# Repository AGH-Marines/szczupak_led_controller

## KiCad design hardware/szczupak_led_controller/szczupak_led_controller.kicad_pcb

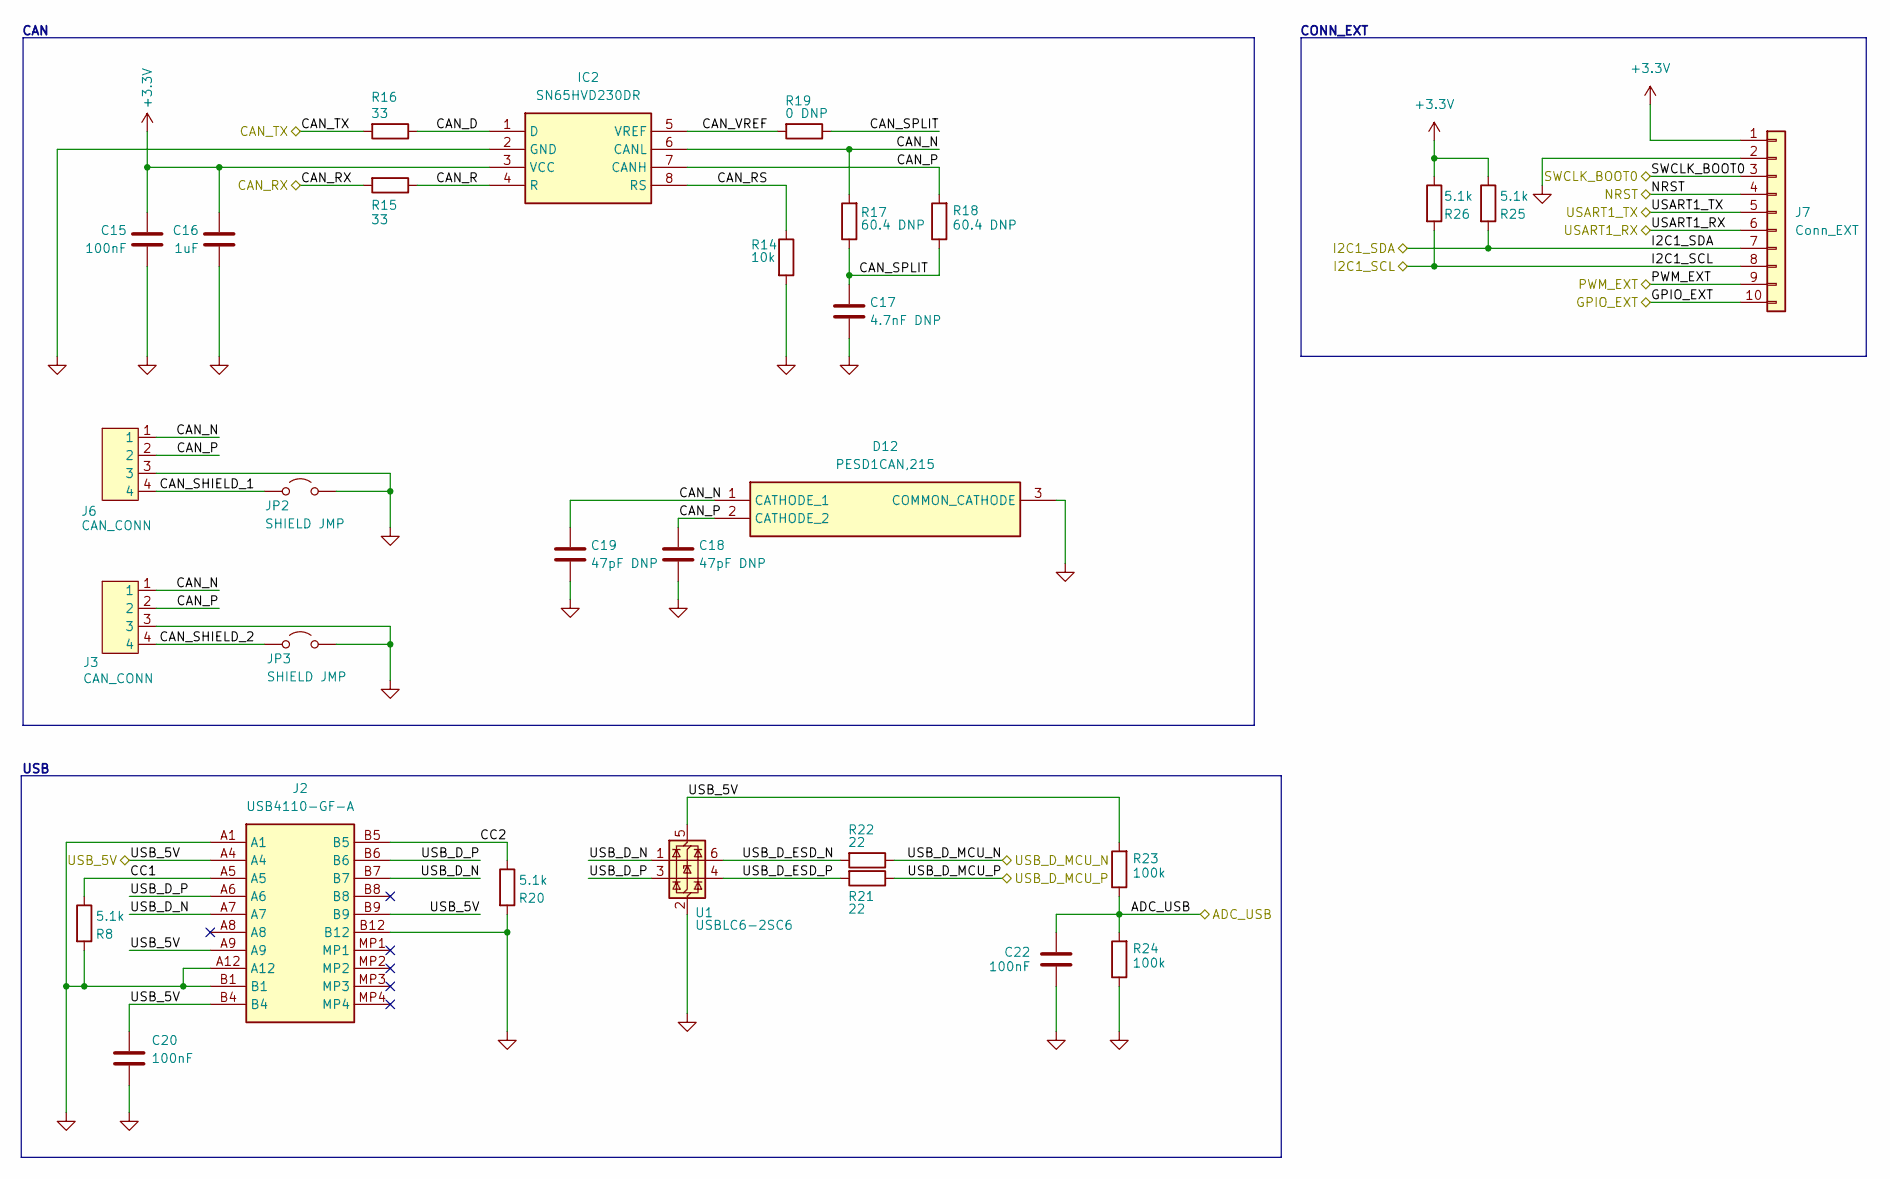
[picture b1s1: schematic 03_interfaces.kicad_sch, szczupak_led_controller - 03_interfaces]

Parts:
C15, C20, C22: 100nF; C_0603_1608Metric
C16: 1uF; C_0805_2012Metric
C17: 4.7nF DNP; C_0603_1608Metric
C18, C19: 47pF DNP; C_0603_1608Metric
D12: PESD1CAN,215; SOT95P230X110-3N; Manufacturer_Part_Number PESD1CAN,215
IC2: SN65HVD230DR; SOT127P600X175-8N; Manufacturer_Part_Number SN65HVD230DR; Mouser Part Number 595-SN65HVD230DR
J2: USB4110-GF-A; USB4110GFA; Manufacturer_Part_Number USB4110-GF-A
J3, J6: CAN_CONN; XY2500V-D(5.08)-4PIN
J7: Conn_EXT; PinHeader_1x10_P2.54mm_Vertical
JP2, JP3: SHIELD JMP; SolderJumper-2_P1.3mm_Open_TrianglePad1.0x1.5mm
R8, R20, R25, R26: 5.1k; R_0603_1608Metric
R14: 10k; R_0603_1608Metric
R15, R16: 33; R_0603_1608Metric
R17, R18: 60.4 DNP; R_0805_2012Metric
R19: 0 DNP; R_0603_1608Metric
R21, R22: 22; R_0603_1608Metric
R23, R24: 100k; R_0603_1608Metric
U1: USBLC6-2SC6; SOT-23-6

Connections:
+3.3V: C15.1, C16.1, IC2.3 (VCC), J7.1, R25.1, R26.1; also elsewhere on the board
/03_interfaces/CAN_D: IC2.1 (D), R16.1
/03_interfaces/CAN_N: C19.1, D12.1 (CATHODE_1), IC2.6 (CANL), J3.1, J6.1, R17.2
/03_interfaces/CAN_P: C18.1, D12.2 (CATHODE_2), IC2.7 (CANH), J3.2, J6.2, R18.2
/03_interfaces/CAN_R: IC2.4 (R), R15.1
/03_interfaces/CAN_RS: IC2.8 (RS), R14.1
/03_interfaces/CAN_SHIELD_1: J6.4, JP2.1 (A)
/03_interfaces/CAN_SHIELD_2: J3.4, JP3.1 (A)
/03_interfaces/CAN_SPLIT: C17.1, R17.1, R18.1, R19.1
/03_interfaces/CAN_VREF: IC2.5 (VREF), R19.2
/03_interfaces/CC1: J2.A5, R8.1
/03_interfaces/CC2: J2.B5, R20.1
/03_interfaces/USB_D_ESD_N: R22.2, U1.6 (I/O1)
/03_interfaces/USB_D_ESD_P: R21.2, U1.4 (I/O2)
/03_interfaces/USB_D_N: J2.A7, J2.B7, U1.1 (I/O1)
/03_interfaces/USB_D_P: J2.A6, J2.B6, U1.3 (I/O2)
/ADC_USB: C22.1, R23.1, R24.2; also elsewhere on the board
/CAN_RX: R15.2; also elsewhere on the board
/CAN_TX: R16.2; also elsewhere on the board
/GPIO_EXT: J7.10; also elsewhere on the board
/I2C1_SCL: J7.8, R26.2; also elsewhere on the board
/I2C1_SDA: J7.7, R25.2; also elsewhere on the board
/NRST: J7.4; also elsewhere on the board
/PWM_EXT: J7.9; also elsewhere on the board
/SWCLK_BOOT0: J7.3; also elsewhere on the board
/USART1_RX: J7.6; also elsewhere on the board
/USART1_TX: J7.5; also elsewhere on the board
/USB_5V: C20.1, J2.A4, J2.A9, J2.B4, J2.B9, R23.2, U1.5 (VBUS); also elsewhere on the board
/USB_D_MCU_N: R22.1; also elsewhere on the board
/USB_D_MCU_P: R21.1; also elsewhere on the board
GND: C15.2, C16.2, C17.2, C18.2, C19.2, C20.2, C22.2, D12.3 (COMMON_CATHODE), IC2.2 (GND), J2.A1, J2.A12, J2.B1, J2.B12, J3.3, J6.3, J7.2, JP2.2 (B), JP3.2 (B), R8.2, R14.2, R20.2, R24.1, U1.2 (GND); also elsewhere on the board

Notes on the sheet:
USB
CONN_EXT
CAN

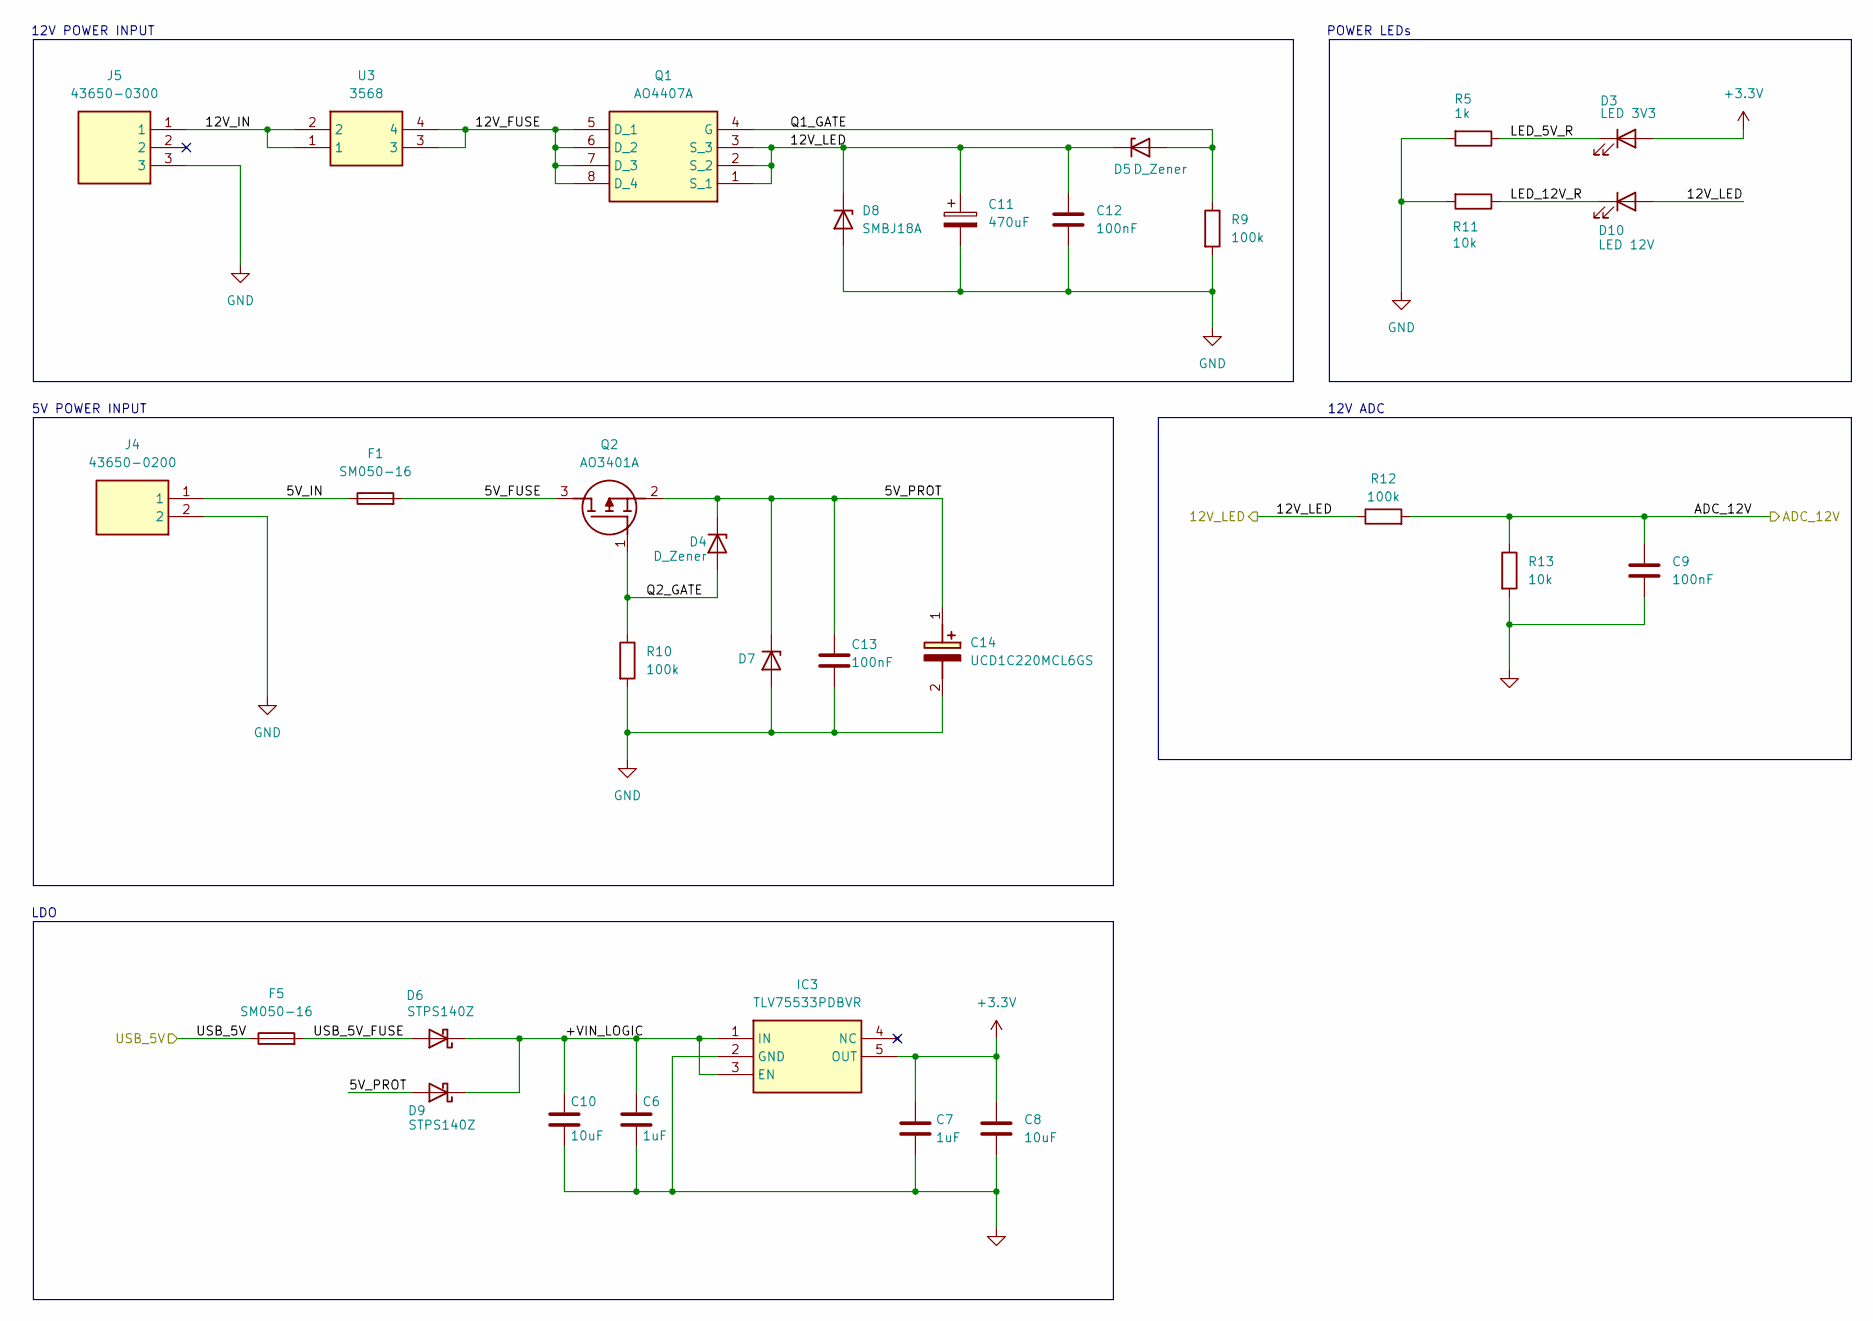
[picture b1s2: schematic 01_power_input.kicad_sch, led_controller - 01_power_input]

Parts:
C6, C7: 1uF; C_0805_2012Metric
C8, C10: 10uF; C_0805_2012Metric
C9, C12, C13: 100nF; C_0603_1608Metric
C11: 470uF; EEEFK1V331P
C14: UCD1C220MCL6GS; CAPAE430X610N; Manufacturer_Part_Number UCD1C220MCL6GS
D3: LED 3V3; LED_0805_2012Metric
D4, D5: D_Zener; D_SOD-123F
D6, D9: STPS140Z; SOD3816X145N; Manufacturer_Part_Number STPS140Z
D7: SMAJ5.0A-E3_61; DIOM5127X229N
D8: SMBJ18A; D_SMB
D10: LED 12V; LED_0805_2012Metric
F1, F5: SM050-16; Fuse_1210_3225Metric
IC3: TLV75533PDBVR; SOT95P280X145-5N; Manufacturer_Part_Number TLV75533PDBVR
J4: 43650-0200; 43650-02_00,01,02_; Manufacturer_Part_Number 43650-0200
J5: 43650-0300; 436500300; Manufacturer_Part_Number 43650-0300
Q1: AO4407A; SOIC127P600X175-8N; Manufacturer_Part_Number AO4407A
Q2: AO3401A; SOT95P280X125-3N; Manufacturer_Part_Number AO3401A
R5: 1k; R_0603_1608Metric
R9, R10, R12: 100k; R_0603_1608Metric
R11, R13: 10k; R_0603_1608Metric
U3: 3568; Manufacturer_Part_Number 3568

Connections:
+3.3V: C7.1, C8.1, D3.2 (A), IC3.5 (OUT); also elsewhere on the board
/01_power_input/5V_FUSE: F1.2, Q2.3 (D)
/01_power_input/5V_IN: F1.1, J4.1
/01_power_input/5V_PROT: C13.1, C14.1 (+), D4.1 (K), D7.1 (K), D9.2 (A), Q2.2 (S)
/01_power_input/12V_FUSE: Q1.5 (D_1), Q1.6 (D_2), Q1.7 (D_3), Q1.8 (D_4), U3.3, U3.4
/01_power_input/12V_IN: J5.1, U3.1, U3.2
/01_power_input/+VIN_LOGIC: C6.1, C10.1, D6.1 (K), D9.1 (K), IC3.1 (IN), IC3.3 (EN)
/01_power_input/LED_5V_R: D3.1 (K), R5.1
/01_power_input/LED_12V_R: D10.1 (K), R11.1
/01_power_input/Q1_GATE: D5.2 (A), Q1.4 (G), R9.1
/01_power_input/Q2_GATE: D4.2 (A), Q2.1 (G), R10.1
/01_power_input/USB_5V_FUSE: D6.2 (A), F5.2
/12V_LED: C11.1, C12.1, D5.1 (K), D8.1 (K), D10.2 (A), Q1.1 (S_1), Q1.2 (S_2), Q1.3 (S_3), R12.1; also elsewhere on the board
/ADC_12V: C9.1, R12.2, R13.1; also elsewhere on the board
/USB_5V: F5.1; also elsewhere on the board
GND: C6.2, C7.2, C8.2, C9.2, C10.2, C11.2, C12.2, C13.2, C14.2 (-), D7.2 (A), D8.2 (A), IC3.2 (GND), J4.2, J5.3, R5.2, R9.2, R10.2, R11.2, R13.2; also elsewhere on the board

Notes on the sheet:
POWER LEDs
12V ADC
5V POWER INPUT
LDO
12V POWER INPUT

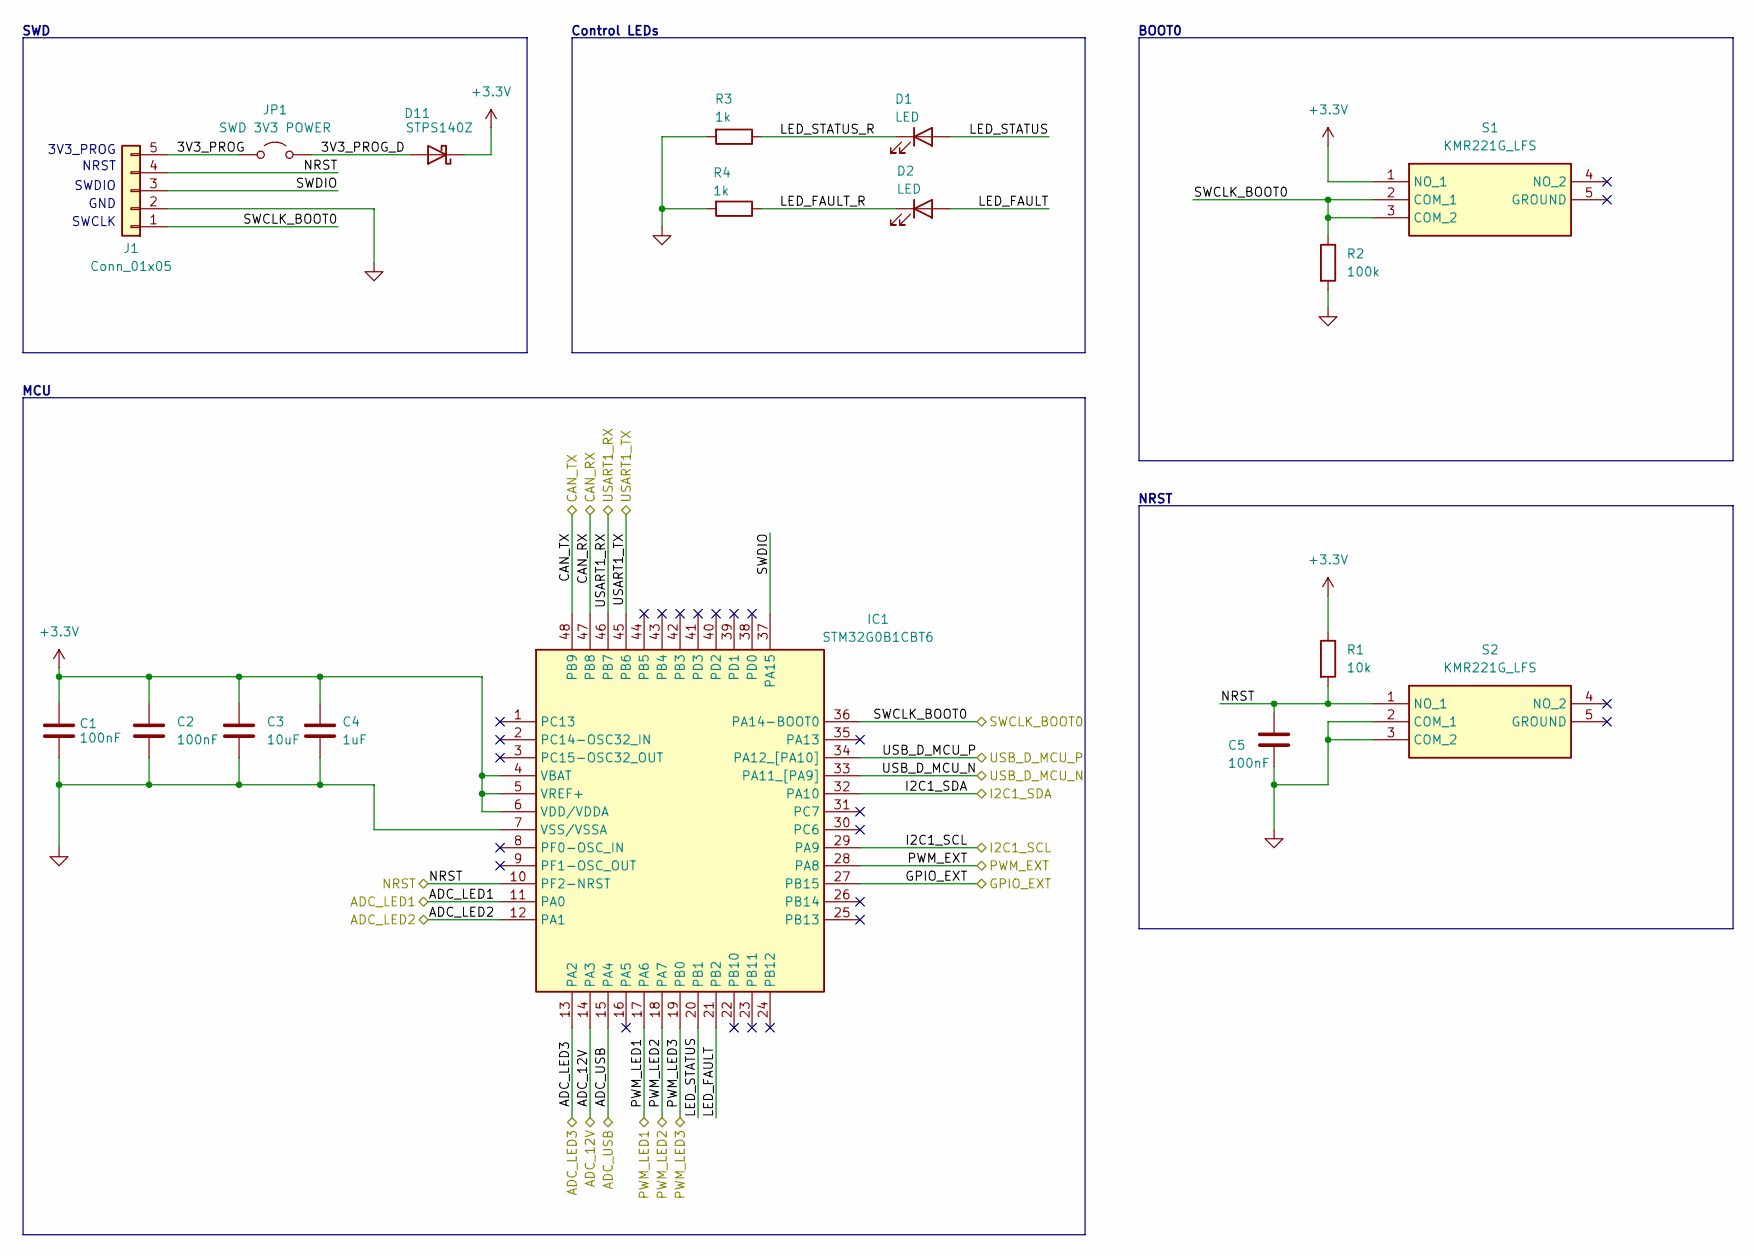
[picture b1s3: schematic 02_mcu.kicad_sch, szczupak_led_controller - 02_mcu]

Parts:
C1, C2, C5: 100nF; C_0603_1608Metric
C3: 10uF; C_0805_2012Metric
C4: 1uF; C_0805_2012Metric
D1, D2: LED; LED_0805_2012Metric
D11: STPS140Z; SOD3816X145N; Manufacturer_Part_Number STPS140Z
IC1: STM32G0B1CBT6; QFP50P900X900X160-48N; Manufacturer_Part_Number STM32G0B1CBT6
J1: Conn_01x05; PinHeader_1x05_P2.54mm_Vertical
JP1: SWD 3V3 POWER; SolderJumper-2_P1.3mm_Open_TrianglePad1.0x1.5mm
R1: 10k; R_0603_1608Metric
R2: 100k; R_0603_1608Metric
R3, R4: 1k; R_0603_1608Metric
S1, S2: KMR221G_LFS; KMR221GLFS; Manufacturer_Part_Number KMR221G LFS

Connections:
+3.3V: C1.1, C2.1, C3.1, C4.1, D11.1 (K), IC1.4 (VBAT), IC1.5 (VREF+), IC1.6 (VDD/VDDA), R1.1, S1.1 (NO_1); also elsewhere on the board
/02_mcu/3V3_PROG: J1.5, JP1.1 (A)
/02_mcu/3V3_PROG_D: D11.2 (A), JP1.2 (B)
/02_mcu/LED_FAULT: D2.2 (A), IC1.21 (PB2)
/02_mcu/LED_FAULT_R: D2.1 (K), R4.1
/02_mcu/LED_STATUS: D1.2 (A), IC1.20 (PB1)
/02_mcu/LED_STATUS_R: D1.1 (K), R3.1
/02_mcu/SWDIO: IC1.37 (PA15), J1.3
/ADC_12V: IC1.14 (PA3); also elsewhere on the board
/ADC_LED1: IC1.11 (PA0); also elsewhere on the board
/ADC_LED2: IC1.12 (PA1); also elsewhere on the board
/ADC_LED3: IC1.13 (PA2); also elsewhere on the board
/ADC_USB: IC1.15 (PA4); also elsewhere on the board
/CAN_RX: IC1.47 (PB8); also elsewhere on the board
/CAN_TX: IC1.48 (PB9); also elsewhere on the board
/GPIO_EXT: IC1.27 (PB15); also elsewhere on the board
/I2C1_SCL: IC1.29 (PA9); also elsewhere on the board
/I2C1_SDA: IC1.32 (PA10); also elsewhere on the board
/NRST: C5.1, IC1.10 (PF2-NRST), J1.4, R1.2, S2.1 (NO_1); also elsewhere on the board
/PWM_EXT: IC1.28 (PA8); also elsewhere on the board
/PWM_LED1: IC1.17 (PA6); also elsewhere on the board
/PWM_LED2: IC1.18 (PA7); also elsewhere on the board
/PWM_LED3: IC1.19 (PB0); also elsewhere on the board
/SWCLK_BOOT0: IC1.36 (PA14-BOOT0), J1.1, R2.1, S1.2 (COM_1), S1.3 (COM_2); also elsewhere on the board
/USART1_RX: IC1.46 (PB7); also elsewhere on the board
/USART1_TX: IC1.45 (PB6); also elsewhere on the board
/USB_D_MCU_N: IC1.33 (PA11_[PA9]); also elsewhere on the board
/USB_D_MCU_P: IC1.34 (PA12_[PA10]); also elsewhere on the board
GND: C1.2, C2.2, C3.2, C4.2, C5.2, IC1.7 (VSS/VSSA), J1.2, R2.2, R3.2, R4.2, S2.2 (COM_1), S2.3 (COM_2); also elsewhere on the board

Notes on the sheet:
SWCLK
MCU
BOOT0
Control LEDs
NRST
SWDIO
NRST
SWD
3V3_PROG
GND

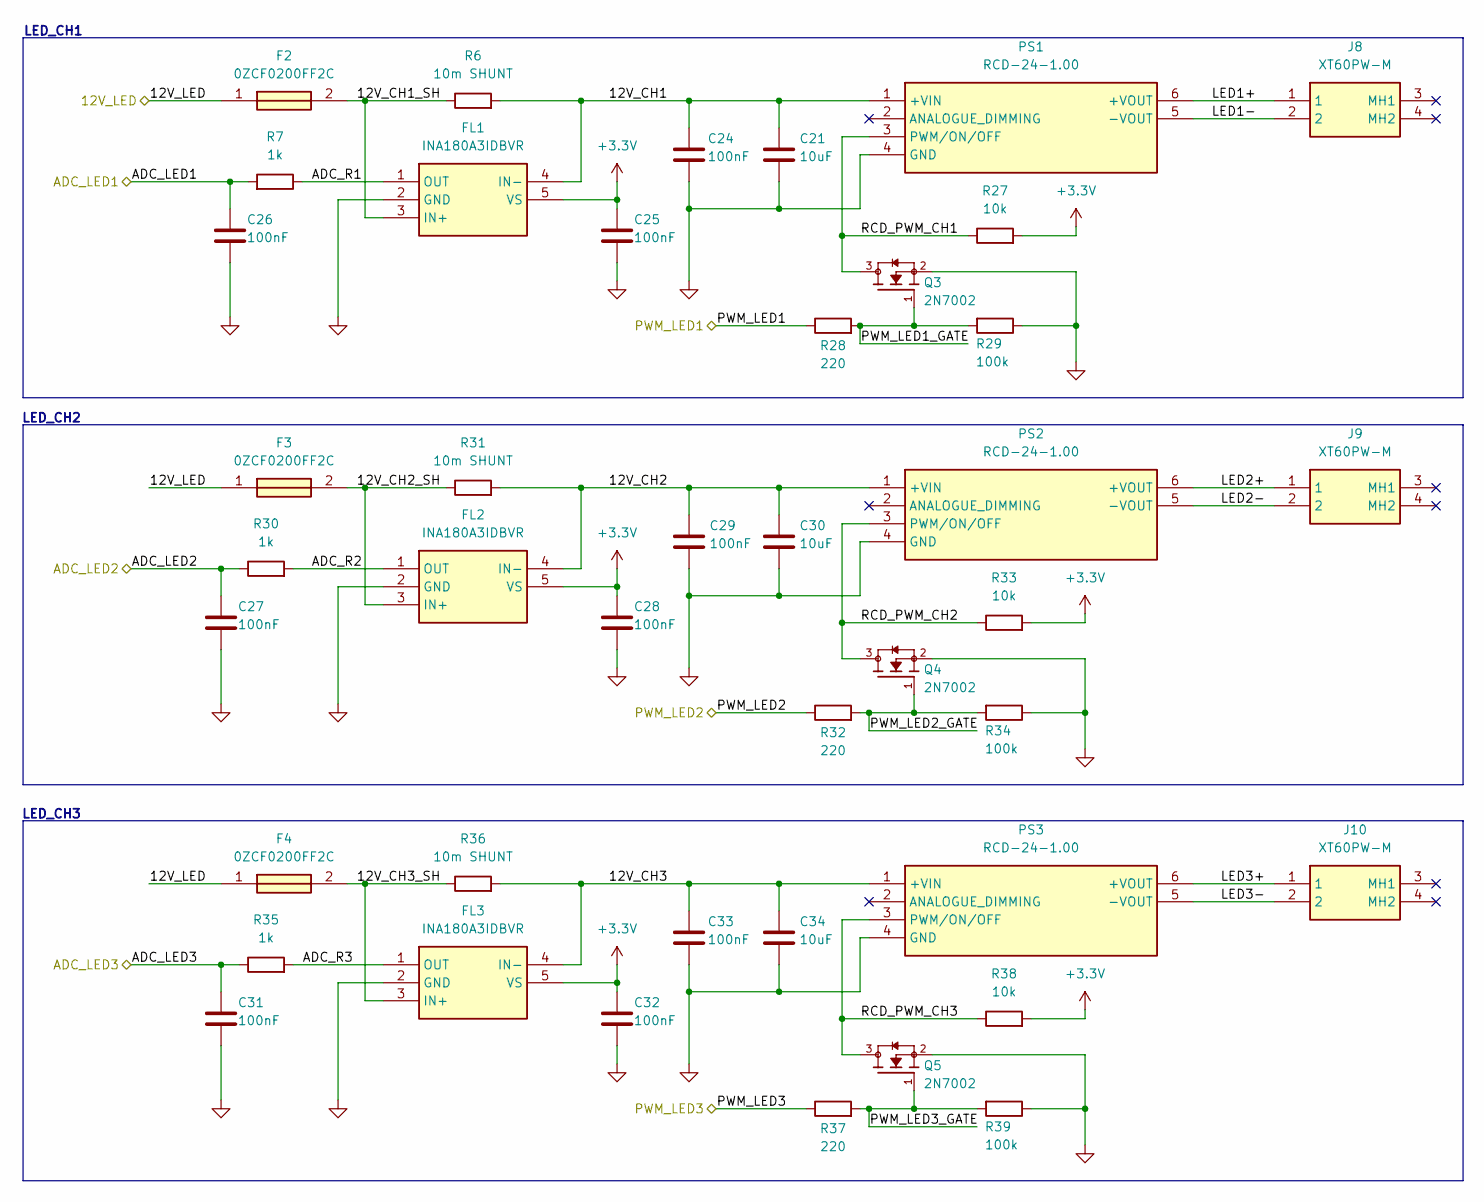
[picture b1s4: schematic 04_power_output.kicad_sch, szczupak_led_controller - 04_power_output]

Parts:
C21, C30, C34: 10uF; C_0805_2012Metric
C24, C25, C26, C27, C28, C29, C31, C32, C33: 100nF; C_0603_1608Metric
F2, F3, F4: 0ZCF0200FF2C; FUSC7451X90N; Manufacturer_Part_Number 0ZCF0200FF2C
FL1, FL2, FL3: INA180A3IDBVR; SOT95P280X145-5N; Manufacturer_Part_Number INA180A3IDBVR
J8, J9, J10: XT60PW-M; XT60PWM_shorter; Manufacturer_Part_Number XT60PW-M
PS1, PS2, PS3: RCD-24-1.00; RCD24030; Manufacturer_Part_Number RCD-24-1.00
Q3, Q4, Q5: 2N7002; TRANS_2N7002; PARTREV 2023-01-11
R6, R31, R36: 10m SHUNT; R_2512_6332Metric
R7, R30, R35: 1k; R_0603_1608Metric
R27, R33, R38: 10k; R_0603_1608Metric
R28, R32, R37: 220; R_0603_1608Metric
R29, R34, R39: 100k; R_0603_1608Metric

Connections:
+3.3V: C25.1, C28.1, C32.1, FL1.5 (VS), FL2.5 (VS), FL3.5 (VS), R27.2, R33.2, R38.2; also elsewhere on the board
/04_power_output/12V_CH1: C21.1, C24.1, FL1.4 (IN-), PS1.1 (+VIN), R6.2
/04_power_output/12V_CH1_SH: F2.2, FL1.3 (IN+), R6.1
/04_power_output/12V_CH2: C29.1, C30.1, FL2.4 (IN-), PS2.1 (+VIN), R31.2
/04_power_output/12V_CH2_SH: F3.2, FL2.3 (IN+), R31.1
/04_power_output/12V_CH3: C33.1, C34.1, FL3.4 (IN-), PS3.1 (+VIN), R36.2
/04_power_output/12V_CH3_SH: F4.2, FL3.3 (IN+), R36.1
/04_power_output/ADC_R1: FL1.1 (OUT), R7.1
/04_power_output/ADC_R2: FL2.1 (OUT), R30.2
/04_power_output/ADC_R3: FL3.1 (OUT), R35.2
/04_power_output/LED1+: J8.1, PS1.6 (+VOUT)
/04_power_output/LED1-: J8.2, PS1.5 (-VOUT)
/04_power_output/LED2+: J9.1, PS2.6 (+VOUT)
/04_power_output/LED2-: J9.2, PS2.5 (-VOUT)
/04_power_output/LED3+: J10.1, PS3.6 (+VOUT)
/04_power_output/LED3-: J10.2, PS3.5 (-VOUT)
/04_power_output/PWM_LED1_GATE: Q3.1, R28.2, R29.2
/04_power_output/PWM_LED2_GATE: Q4.1, R32.2, R34.2
/04_power_output/PWM_LED3_GATE: Q5.1, R37.2, R39.2
/04_power_output/RCD_PWM_CH1: PS1.3 (PWM/ON/OFF), Q3.3, R27.1
/04_power_output/RCD_PWM_CH2: PS2.3 (PWM/ON/OFF), Q4.3, R33.1
/04_power_output/RCD_PWM_CH3: PS3.3 (PWM/ON/OFF), Q5.3, R38.1
/12V_LED: F2.1, F3.1, F4.1; also elsewhere on the board
/ADC_LED1: C26.1, R7.2; also elsewhere on the board
/ADC_LED2: C27.1, R30.1; also elsewhere on the board
/ADC_LED3: C31.1, R35.1; also elsewhere on the board
/PWM_LED1: R28.1; also elsewhere on the board
/PWM_LED2: R32.1; also elsewhere on the board
/PWM_LED3: R37.1; also elsewhere on the board
GND: C21.2, C24.2, C25.2, C26.2, C27.2, C28.2, C29.2, C30.2, C31.2, C32.2, C33.2, C34.2, FL1.2 (GND), FL2.2 (GND), FL3.2 (GND), PS1.4 (GND), PS2.4 (GND), PS3.4 (GND), Q3.2, Q4.2, Q5.2, R29.1, R34.1, R39.1; also elsewhere on the board

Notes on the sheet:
LED_CH1
LED_CH2
LED_CH3

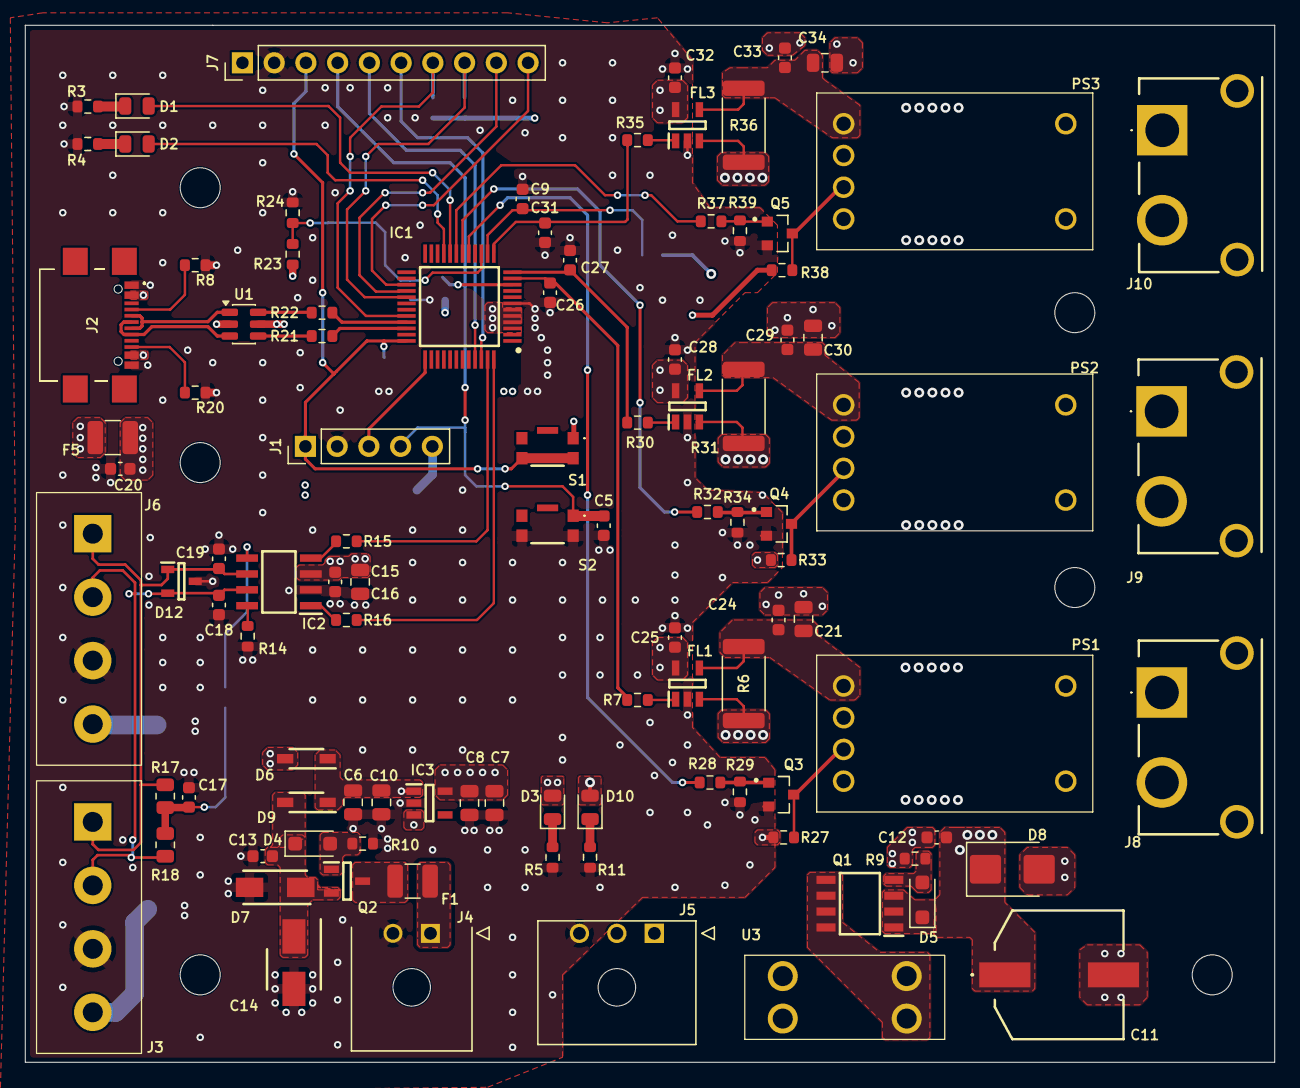
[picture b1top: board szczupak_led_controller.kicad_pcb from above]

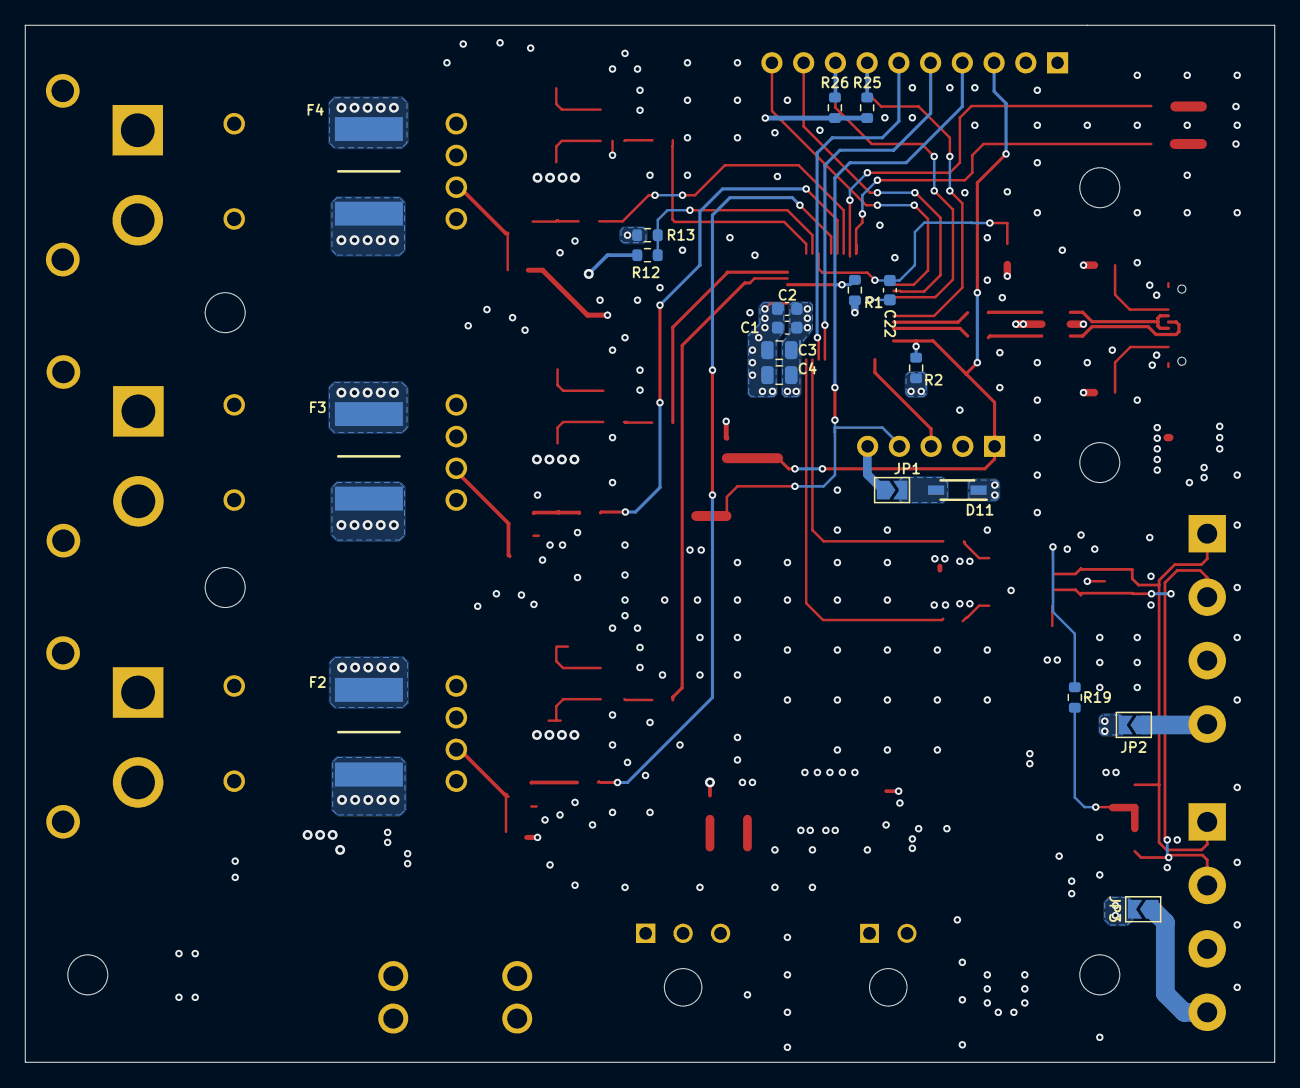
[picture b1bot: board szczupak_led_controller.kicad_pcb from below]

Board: 4 copper layers, 100.0 x 83.0 mm, 120 parts (19 on the bottom side), 78 nets.
